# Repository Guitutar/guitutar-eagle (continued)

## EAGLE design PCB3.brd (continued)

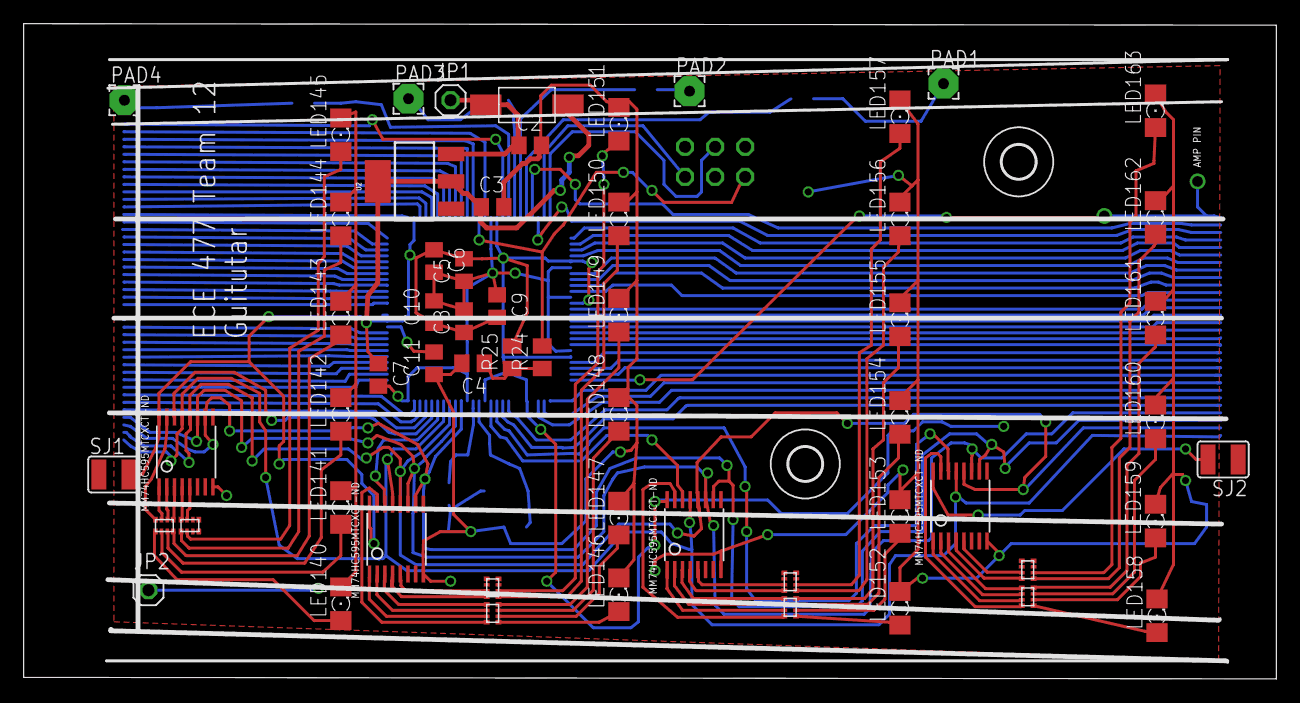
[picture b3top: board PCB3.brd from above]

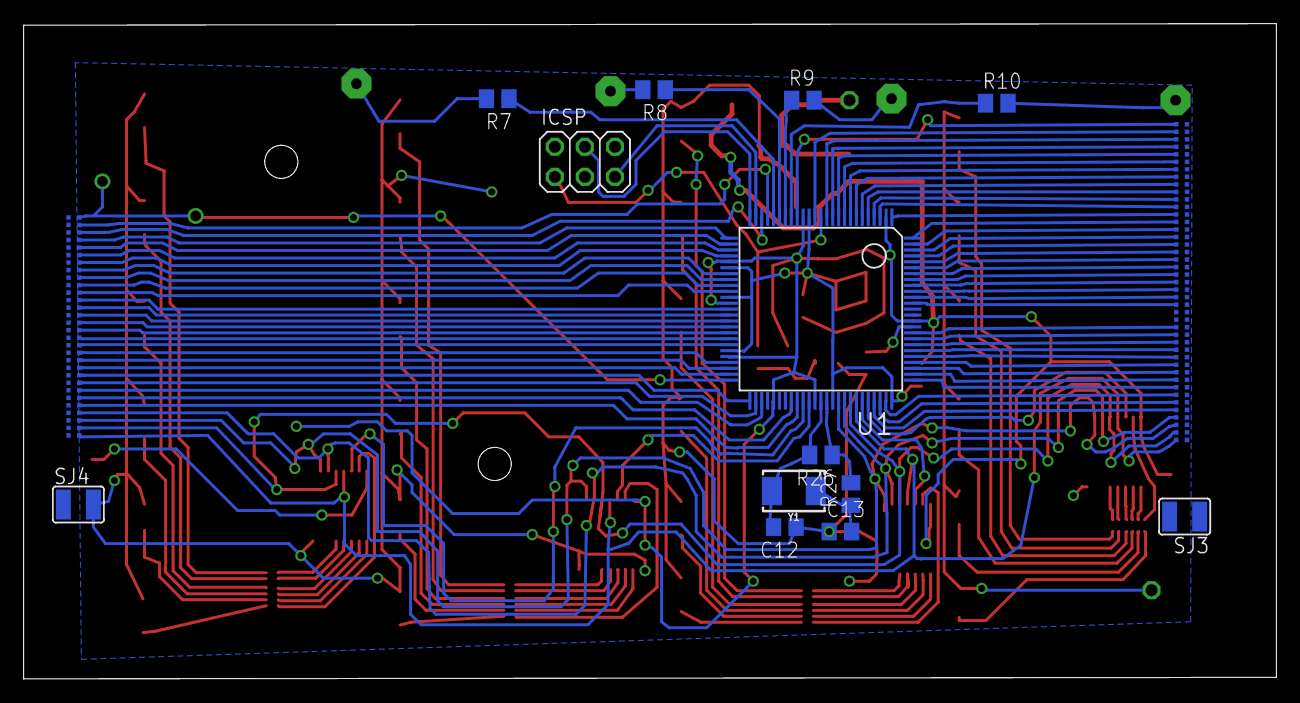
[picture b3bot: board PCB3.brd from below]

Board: 2 copper layers, 105.8 x 55.4 mm, 146 parts (86 on the bottom side), 141 nets.

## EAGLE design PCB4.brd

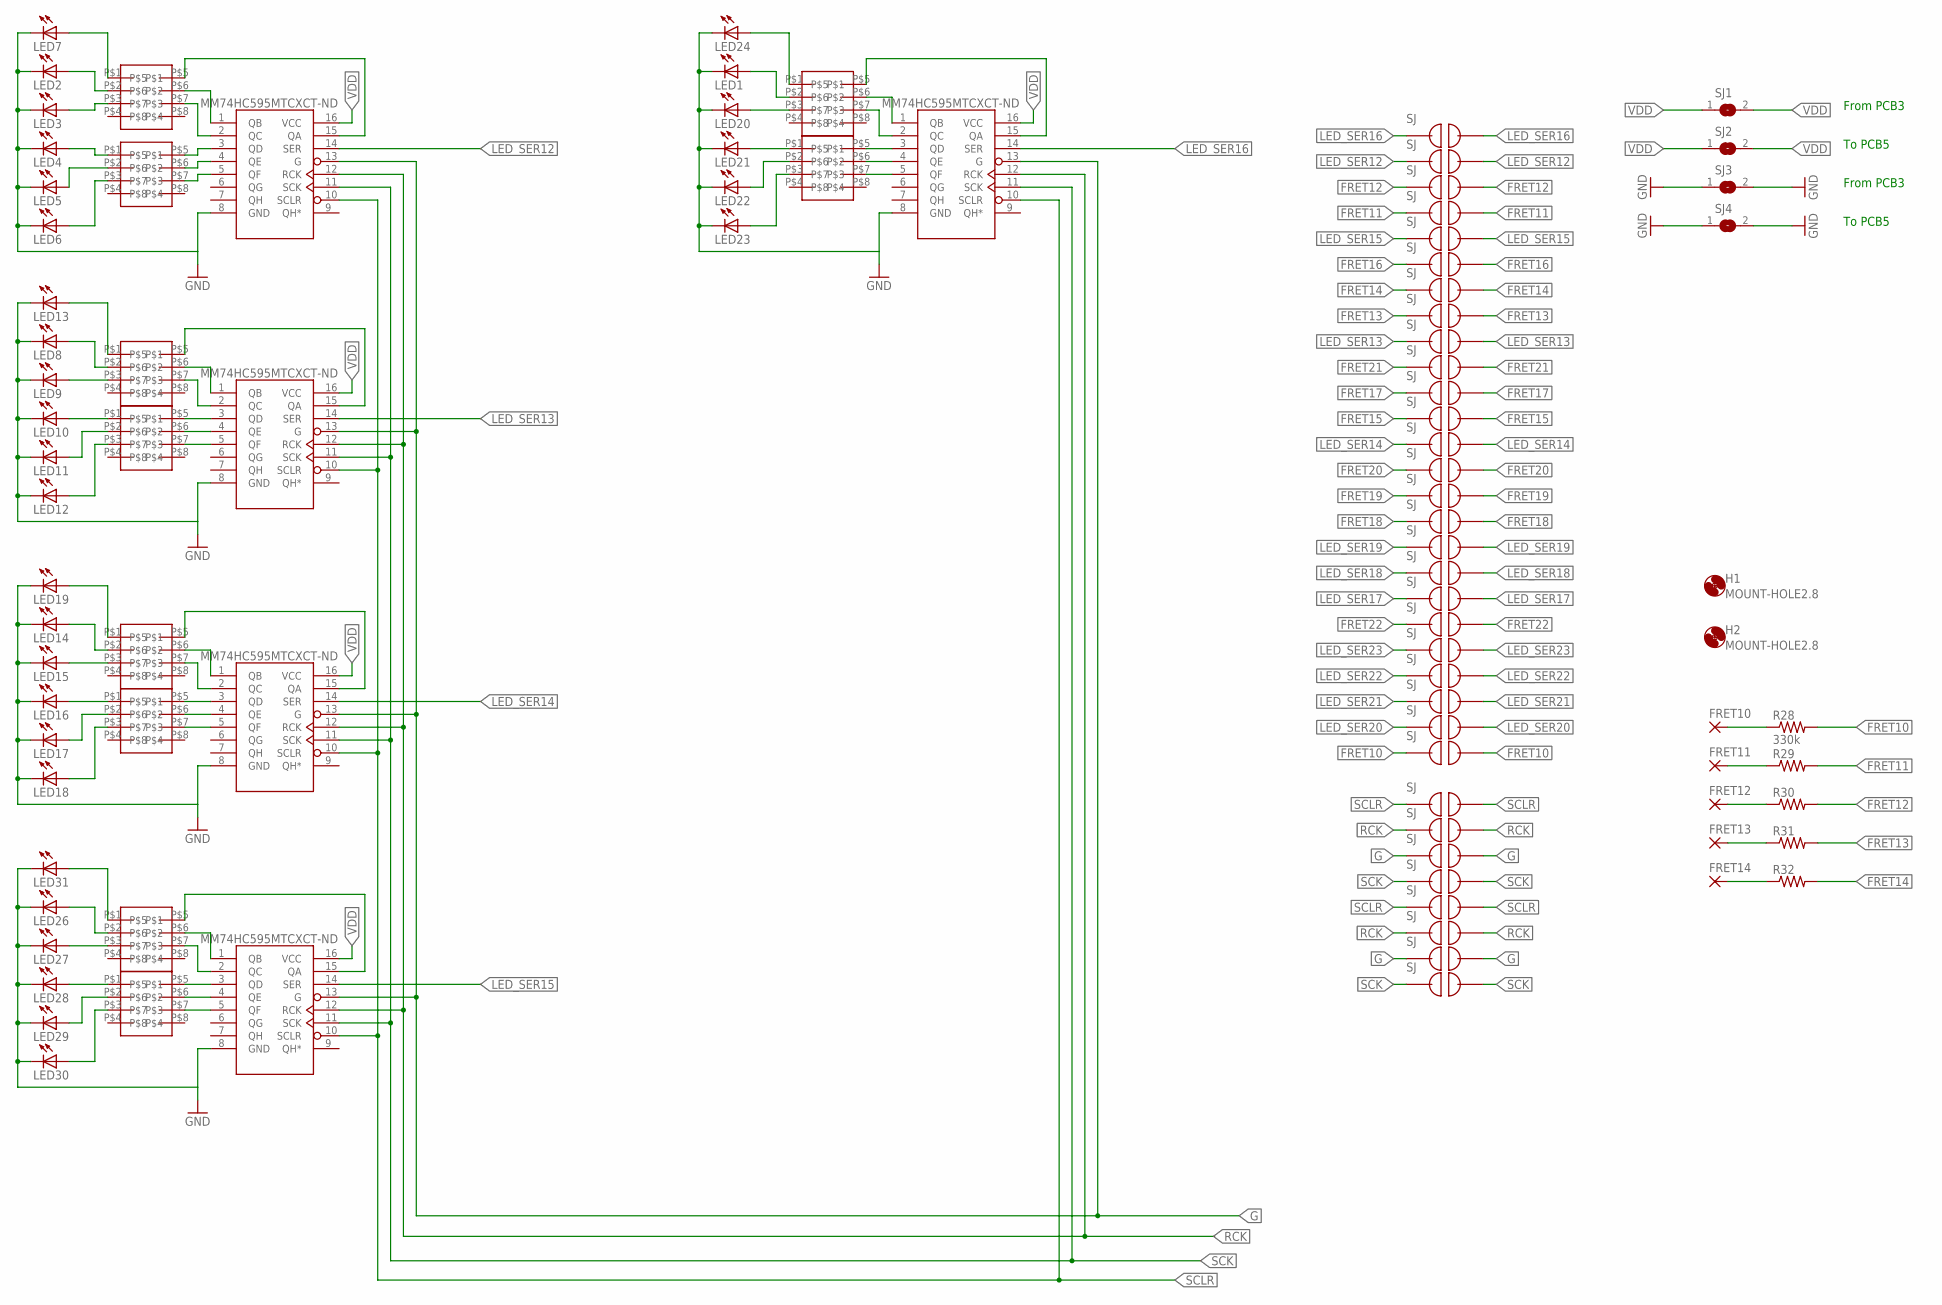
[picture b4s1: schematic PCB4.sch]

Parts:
FRET10, FRET11, FRET12, FRET13, FRET14: 2,54/0,9
H1, H2: MOUNT-HOLE2.8; 2,8
LED1, LED2, LED3, LED4, LED5, LED6, LED7, LED8, LED9, LED10, LED11, LED12, LED13, LED14, LED15, LED16, LED17, LED18, LED19, LED20, LED21, LED22, LED23, LED24, LED26, LED27, LED28, LED29, LED30, LED31: LEDSMT1206; 1206
R28: 330k; R0805
R29, R30, R31, R32: R-US_R0805; R0805
SJ1, SJ2, SJ3, SJ4: SJ
U$1, U$2, U$3, U$4, U$5: MM74HC595TSSOP-LD16; MM74HC595MTCXCT-ND
U$6, U$7, U$8, U$9, U$10, U$11, U$12, U$13, U$14, U$15: MNR04MRAPJ680; MNR04
U$19, U$42, U$45, U$46, U$47, U$48, U$49, U$50, U$51, U$52, U$53, U$54, U$55, U$56, U$57, U$58, U$59, U$60, U$61, U$62, U$63, U$64, U$65, U$66, U$67, U$68, U$69, U$79, U$80, U$81, U$82, U$83, U$84: JUMPER

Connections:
FRET10: R28.2, U$69.P$1, U$69.P$2
FRET11: R29.2, U$48.P$1, U$48.P$2
FRET12: R30.2, U$47.P$1, U$47.P$2
FRET13: R31.2, U$52.P$1, U$52.P$2
FRET14: R32.2, U$51.P$1, U$51.P$2
FRET15: U$56.P$1, U$56.P$2
FRET16: U$50.P$1, U$50.P$2
FRET17: U$55.P$1, U$55.P$2
FRET18: U$60.P$1, U$60.P$2
FRET19: U$59.P$1, U$59.P$2
FRET20: U$58.P$1, U$58.P$2
FRET21: U$54.P$1, U$54.P$2
FRET22: U$64.P$1, U$64.P$2
G: U$1.13 (G), U$2.13 (G), U$3.13 (G), U$4.13 (G), U$5.13 (G), U$80.P$1, U$80.P$2, U$84.P$1, U$84.P$2
GND: LED1.C, LED2.C, LED3.C, LED4.C, LED5.C, LED6.C, LED7.C, LED8.C, LED9.C, LED10.C, LED11.C, LED12.C, LED13.C, LED14.C, LED15.C, LED16.C, LED17.C, LED18.C, LED19.C, LED20.C, LED21.C, LED22.C, LED23.C, LED24.C, LED26.C, LED27.C, LED28.C, LED29.C, LED30.C, LED31.C, SJ3.1, SJ3.2, SJ4.1, SJ4.2, U$1.8 (GND), U$2.8 (GND), U$3.8 (GND), U$4.8 (GND), U$5.8 (GND)
LED_SER12: U$4.14 (SER), U$46.P$1, U$46.P$2
LED_SER13: U$1.14 (SER), U$53.P$1, U$53.P$2
LED_SER14: U$3.14 (SER), U$57.P$1, U$57.P$2
LED_SER15: U$5.14 (SER), U$49.P$1, U$49.P$2
LED_SER16: U$2.14 (SER), U$45.P$1, U$45.P$2
LED_SER17: U$63.P$1, U$63.P$2
LED_SER18: U$62.P$1, U$62.P$2
LED_SER19: U$61.P$1, U$61.P$2
LED_SER20: U$68.P$1, U$68.P$2
LED_SER21: U$67.P$1, U$67.P$2
LED_SER22: U$66.P$1, U$66.P$2
LED_SER23: U$65.P$1, U$65.P$2
unnamed: LED2.A, U$6.P$2
unnamed: U$4.1 (QB), U$6.P$6
unnamed: LED3.A, U$6.P$3
unnamed: U$4.2 (QC), U$6.P$7
unnamed: LED4.A, U$7.P$1
unnamed: LED7.A, U$6.P$1
unnamed: U$4.15 (QA), U$6.P$5
unnamed: LED5.A, U$7.P$2
unnamed: U$4.3 (QD), U$7.P$5
unnamed: U$4.4 (QE), U$7.P$6
unnamed: U$4.5 (QF), U$7.P$7
unnamed: LED6.A, U$7.P$3
unnamed: LED13.A, U$8.P$1
unnamed: LED8.A, U$8.P$2
unnamed: U$1.1 (QB), U$8.P$6
unnamed: U$1.2 (QC), U$8.P$7
unnamed: LED9.A, U$8.P$3
unnamed: LED10.A, U$9.P$1
unnamed: U$1.3 (QD), U$9.P$5
unnamed: LED11.A, U$9.P$2
unnamed: U$1.4 (QE), U$9.P$6
unnamed: U$1.5 (QF), U$9.P$7
unnamed: LED12.A, U$9.P$3
unnamed: U$1.15 (QA), U$8.P$5
unnamed: LED19.A, U$10.P$1
unnamed: LED14.A, U$10.P$2
unnamed: U$3.1 (QB), U$10.P$6
unnamed: U$3.2 (QC), U$10.P$7
unnamed: LED15.A, U$10.P$3
unnamed: LED16.A, U$11.P$1
unnamed: U$3.3 (QD), U$11.P$5
unnamed: U$3.4 (QE), U$11.P$6
unnamed: U$3.5 (QF), U$11.P$7
unnamed: LED18.A, U$11.P$3
unnamed: LED17.A, U$11.P$2
unnamed: LED31.A, U$12.P$1
unnamed: LED26.A, U$12.P$2
unnamed: LED27.A, U$12.P$3
unnamed: U$5.2 (QC), U$12.P$7
unnamed: U$3.15 (QA), U$10.P$5
unnamed: U$5.1 (QB), U$12.P$6
unnamed: U$5.3 (QD), U$13.P$5
unnamed: U$5.4 (QE), U$13.P$6
unnamed: U$5.5 (QF), U$13.P$7
unnamed: U$2.15 (QA), U$14.P$5
unnamed: LED28.A, U$13.P$1
unnamed: LED29.A, U$13.P$2
unnamed: LED30.A, U$13.P$3
unnamed: LED24.A, U$14.P$1
unnamed: LED1.A, U$14.P$2
unnamed: LED20.A, U$14.P$3
unnamed: U$2.1 (QB), U$14.P$6
unnamed: U$2.2 (QC), U$14.P$7
unnamed: U$2.3 (QD), U$15.P$5
unnamed: U$2.4 (QE), U$15.P$6
unnamed: U$2.5 (QF), U$15.P$7
unnamed: LED23.A, U$15.P$3
unnamed: FRET10.1, R28.1
unnamed: FRET11.1, R29.1
unnamed: LED22.A, U$15.P$2
unnamed: LED21.A, U$15.P$1
unnamed: FRET12.1, R30.1
unnamed: FRET13.1, R31.1
unnamed: FRET14.1, R32.1
unnamed: U$5.15 (QA), U$12.P$5
RCK: U$1.12 (RCK), U$2.12 (RCK), U$3.12 (RCK), U$4.12 (RCK), U$5.12 (RCK), U$79.P$1, U$79.P$2, U$83.P$1, U$83.P$2
SCK: U$1.11 (SCK), U$2.11 (SCK), U$3.11 (SCK), U$4.11 (SCK), U$5.11 (SCK), U$42.P$1, U$42.P$2, U$81.P$1, U$81.P$2
SCLR: U$1.10 (SCLR), U$2.10 (SCLR), U$3.10 (SCLR), U$4.10 (SCLR), U$5.10 (SCLR), U$19.P$1, U$19.P$2, U$82.P$1, U$82.P$2
VDD: SJ1.1, SJ1.2, SJ2.1, SJ2.2, U$1.16 (VCC), U$2.16 (VCC), U$3.16 (VCC), U$4.16 (VCC), U$5.16 (VCC)

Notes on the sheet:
From PCB3
To PCB5

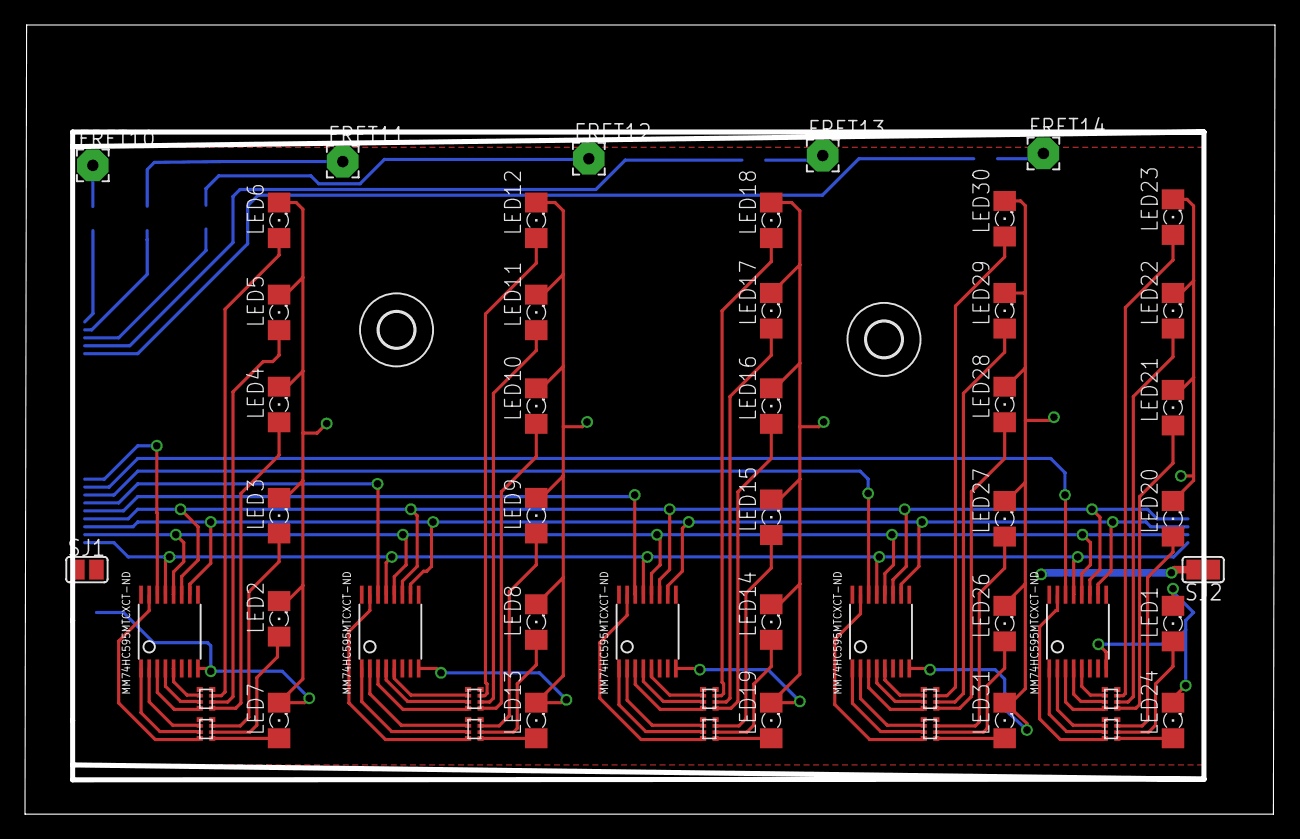
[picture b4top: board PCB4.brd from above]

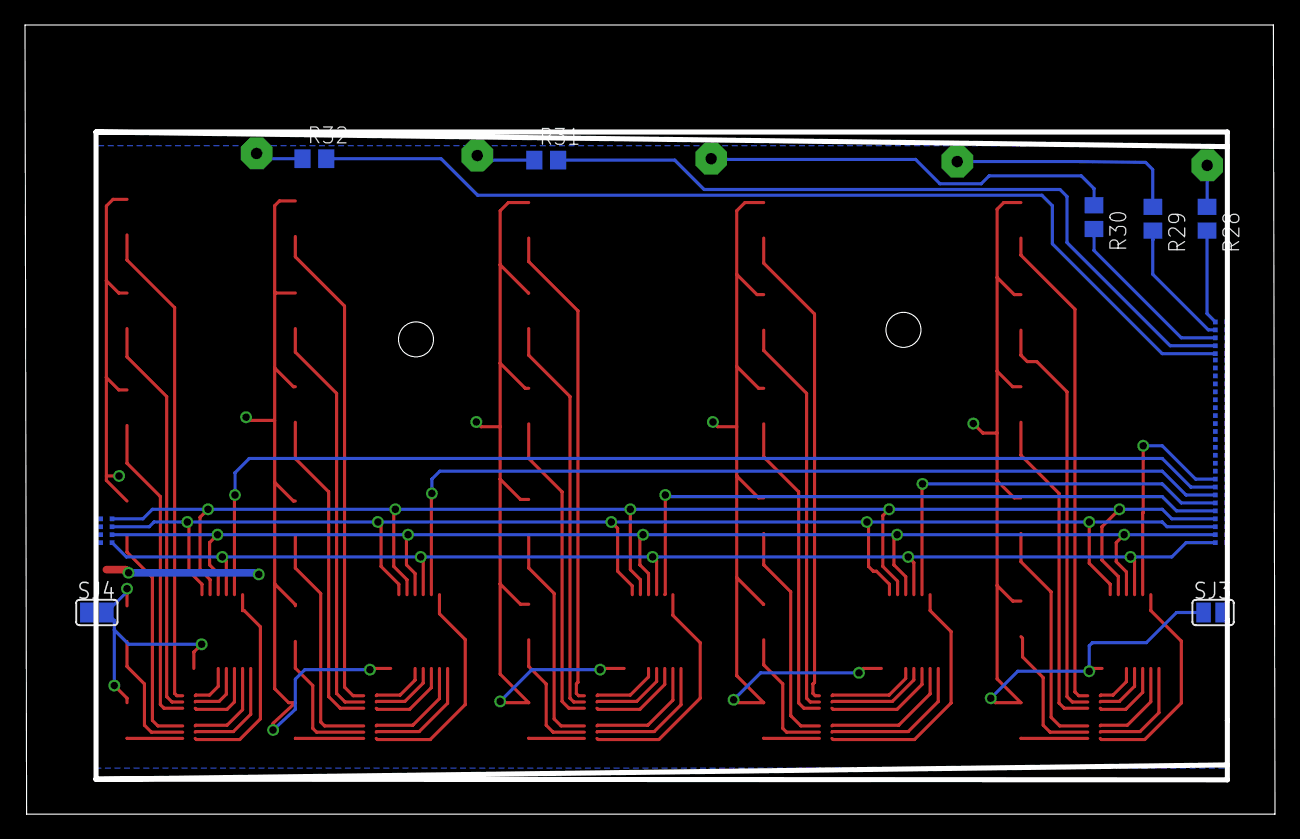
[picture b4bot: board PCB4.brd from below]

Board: 2 copper layers, 100.0 x 63.1 mm, 94 parts (40 on the bottom side), 96 nets.

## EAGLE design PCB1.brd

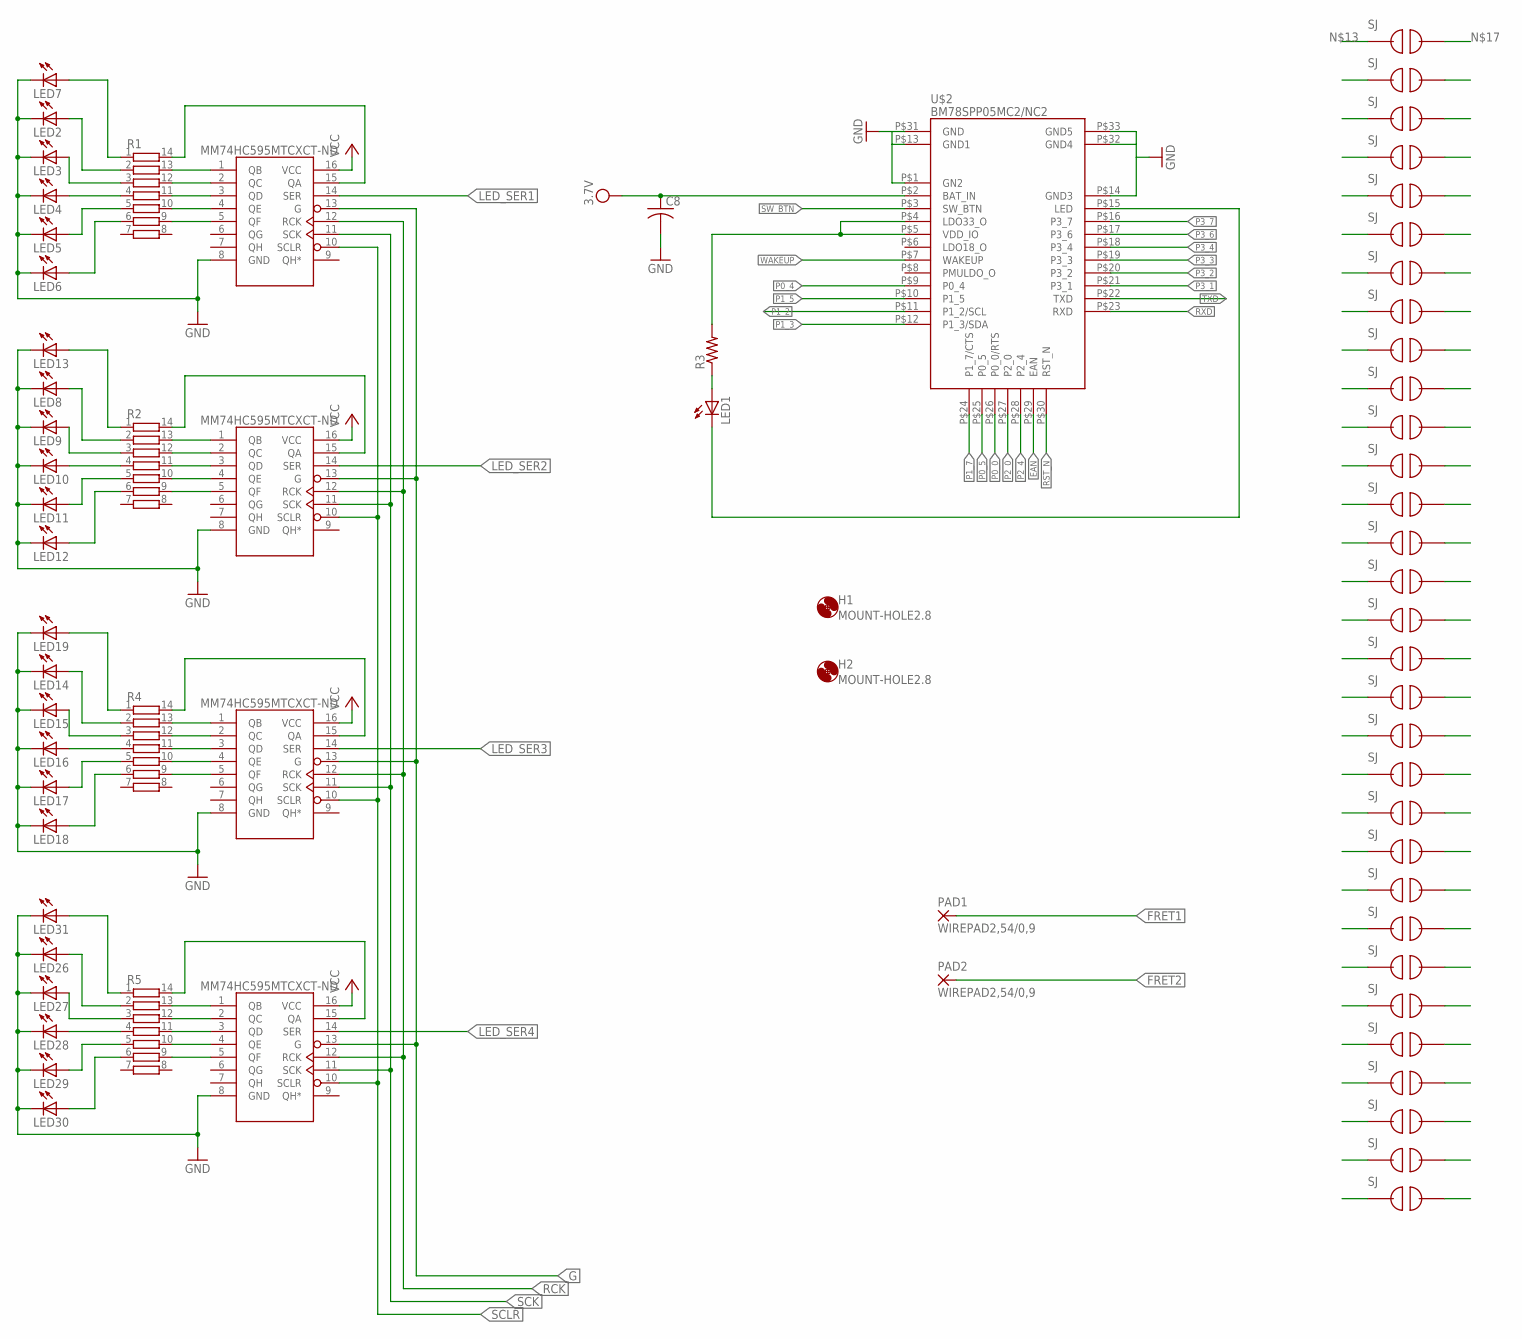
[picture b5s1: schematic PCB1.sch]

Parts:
C8: C-USC0805; C0805
H1, H2: MOUNT-HOLE2.8; 2,8
LED1, LED2, LED3, LED4, LED5, LED6, LED7, LED8, LED9, LED10, LED11, LED12, LED13, LED14, LED15, LED16, LED17, LED18, LED19, LED26, LED27, LED28, LED29, LED30, LED31: LEDSMT1206; 1206
PAD1, PAD2: WIREPAD2,54/0,9; 2,54/0,9
R1, R2, R4, R5: 4814P-T01; 4814P
R3: R-US_M0805; M0805
U$1, U$3, U$4, U$5: MM74HC595TSSOP-LD16; MM74HC595MTCXCT-ND
U$2: BM78SPP05MC2/NC2
U$6, U$7, U$8, U$9, U$10, U$11, U$12, U$13, U$14, U$15, U$16, U$17, U$18, U$19, U$20, U$21, U$22, U$23, U$24, U$25, U$26, U$27, U$28, U$29, U$30, U$31, U$32, U$33, U$34, U$35, U$36: JUMPER

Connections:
EAN: U$2.P$29 (EAN)
FRET1: PAD1.1
FRET2: PAD2.1
G: U$1.13 (G), U$3.13 (G), U$4.13 (G), U$5.13 (G)
GND: C8.2, LED2.C, LED3.C, LED4.C, LED5.C, LED6.C, LED7.C, LED8.C, LED9.C, LED10.C, LED11.C, LED12.C, LED13.C, LED14.C, LED15.C, LED16.C, LED17.C, LED18.C, LED19.C, LED26.C, LED27.C, LED28.C, LED29.C, LED30.C, LED31.C, U$1.8 (GND), U$2.P$1 (GN2), U$2.P$13 (GND1), U$2.P$14 (GND3), U$2.P$31 (GND), U$2.P$32 (GND4), U$2.P$33 (GND5), U$3.8 (GND), U$4.8 (GND), U$5.8 (GND)
LED: LED1.C, U$2.P$15 (LED)
LED_SER1: U$4.14 (SER)
LED_SER2: U$1.14 (SER)
LED_SER3: U$3.14 (SER)
LED_SER4: U$5.14 (SER)
unnamed: R1.13, U$4.1 (QB)
unnamed: R1.12, U$4.2 (QC)
unnamed: R1.11, U$4.3 (QD)
unnamed: R1.10, U$4.4 (QE)
unnamed: R1.9, U$4.5 (QF)
unnamed: LED7.A, R1.1
unnamed: R1.14, U$4.15 (QA)
unnamed: LED2.A, R1.2
unnamed: LED3.A, R1.3
unnamed: LED4.A, R1.4
unnamed: LED5.A, R1.5
unnamed: LED6.A, R1.6
unnamed: LED1.A, R3.1
unnamed: R3.2, U$2.P$4 (LDO33_O), U$2.P$5 (VDD_IO)
unnamed: R2.13, U$1.1 (QB)
unnamed: R2.12, U$1.2 (QC)
unnamed: R2.11, U$1.3 (QD)
unnamed: R2.10, U$1.4 (QE)
unnamed: R2.9, U$1.5 (QF)
unnamed: R2.14, U$1.15 (QA)
unnamed: LED13.A, R2.1
unnamed: LED8.A, R2.2
unnamed: LED9.A, R2.3
unnamed: LED10.A, R2.4
unnamed: LED11.A, R2.5
unnamed: LED12.A, R2.6
unnamed: R4.13, U$3.1 (QB)
unnamed: R4.12, U$3.2 (QC)
unnamed: R4.11, U$3.3 (QD)
unnamed: R4.10, U$3.4 (QE)
unnamed: R4.9, U$3.5 (QF)
unnamed: R4.14, U$3.15 (QA)
unnamed: LED19.A, R4.1
unnamed: LED14.A, R4.2
unnamed: LED15.A, R4.3
unnamed: LED16.A, R4.4
unnamed: LED17.A, R4.5
unnamed: LED18.A, R4.6
unnamed: R5.13, U$5.1 (QB)
unnamed: R5.12, U$5.2 (QC)
unnamed: R5.11, U$5.3 (QD)
unnamed: R5.10, U$5.4 (QE)
unnamed: R5.9, U$5.5 (QF)
unnamed: R5.14, U$5.15 (QA)
unnamed: LED31.A, R5.1
unnamed: LED26.A, R5.2
unnamed: LED27.A, R5.3
unnamed: LED28.A, R5.4
unnamed: LED29.A, R5.5
unnamed: LED30.A, R5.6
P0_0: U$2.P$26 (P0_0/RTS)
P0_4: U$2.P$9 (P0_4)
P0_5: U$2.P$25 (P0_5)
P1_2: U$2.P$11 (P1_2/SCL)
P1_3: U$2.P$12 (P1_3/SDA)
P1_5: U$2.P$10 (P1_5)
P1_7: U$2.P$24 (P1_7/CTS)
P2_0: U$2.P$27 (P2_0)
P2_4: U$2.P$28 (P2_4)
P3_1: U$2.P$21 (P3_1)
P3_2: U$2.P$20 (P3_2)
P3_3: U$2.P$19 (P3_3)
P3_4: U$2.P$18 (P3_4)
P3_6: U$2.P$17 (P3_6)
P3_7: U$2.P$16 (P3_7)
RCK: U$1.12 (RCK), U$3.12 (RCK), U$4.12 (RCK), U$5.12 (RCK)
RST_N: U$2.P$30 (RST_N)
RXD: U$2.P$23 (RXD)
SCK: U$1.11 (SCK), U$3.11 (SCK), U$4.11 (SCK), U$5.11 (SCK)
SCLR: U$1.10 (SCLR), U$3.10 (SCLR), U$4.10 (SCLR), U$5.10 (SCLR)
SW_BTN: U$2.P$3 (SW_BTN)
TXD: U$2.P$22 (TXD)
VCC: U$1.16 (VCC), U$3.16 (VCC), U$4.16 (VCC), U$5.16 (VCC)
VDD: C8.1, U$2.P$2 (BAT_IN)
WAKEUP: U$2.P$7 (WAKEUP)

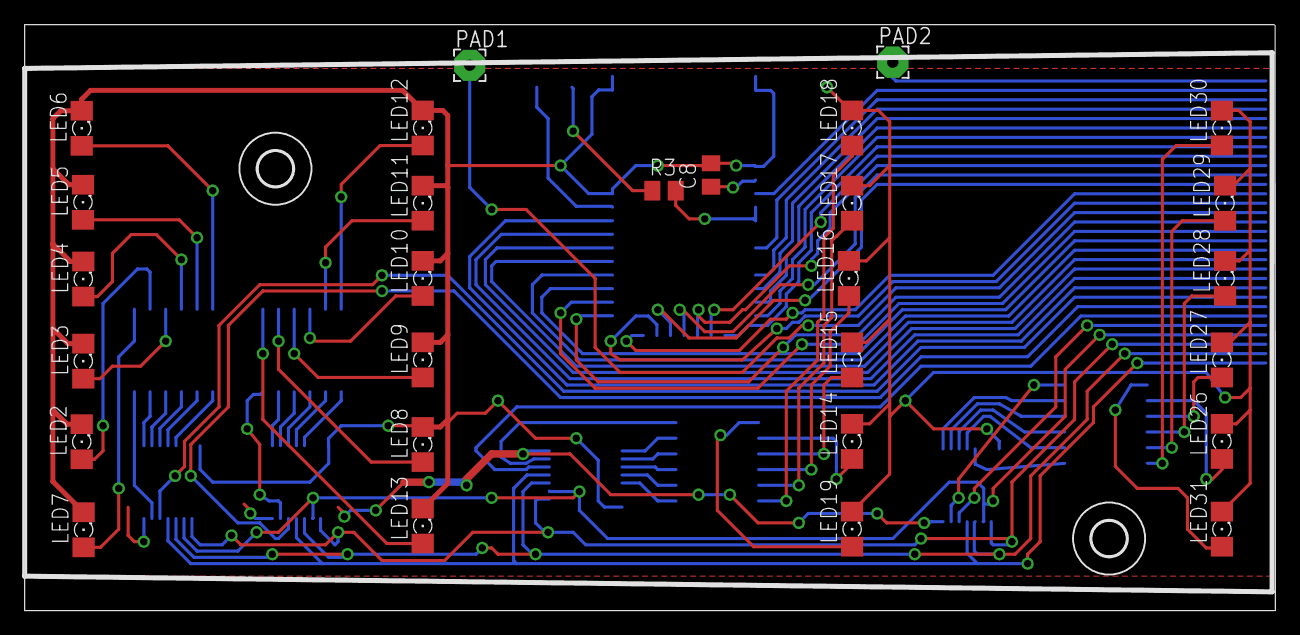
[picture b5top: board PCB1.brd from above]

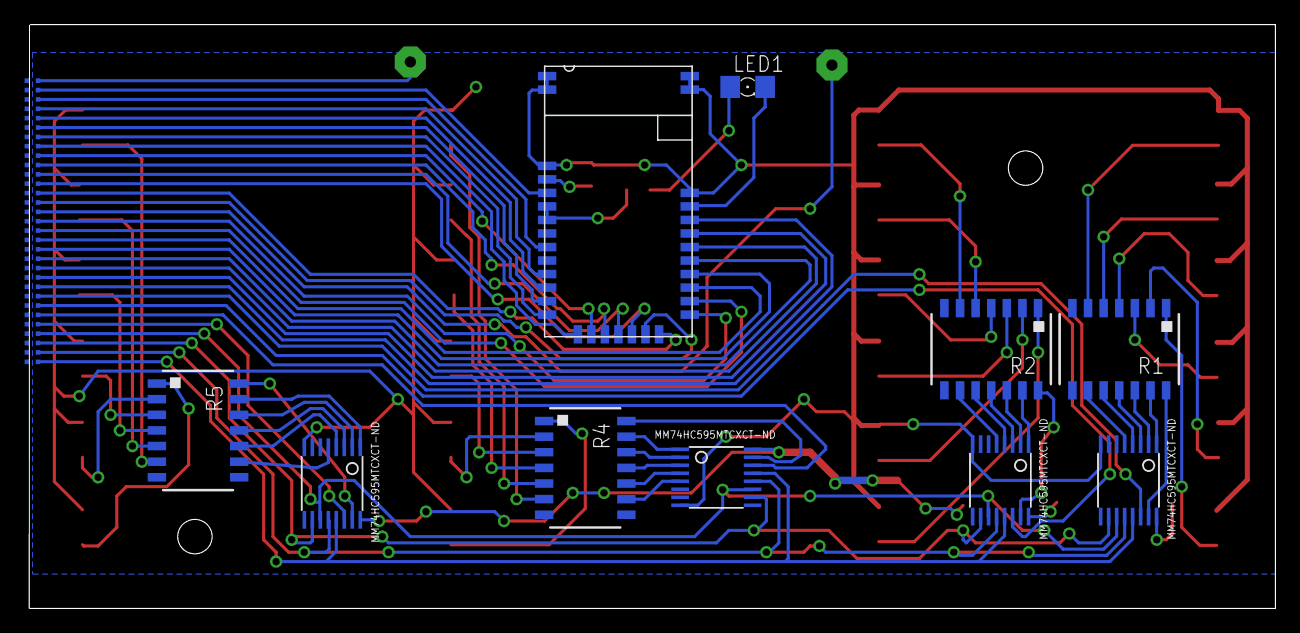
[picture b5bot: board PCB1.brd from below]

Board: 2 copper layers, 101.4 x 47.5 mm, 71 parts (41 on the bottom side), 58 nets.

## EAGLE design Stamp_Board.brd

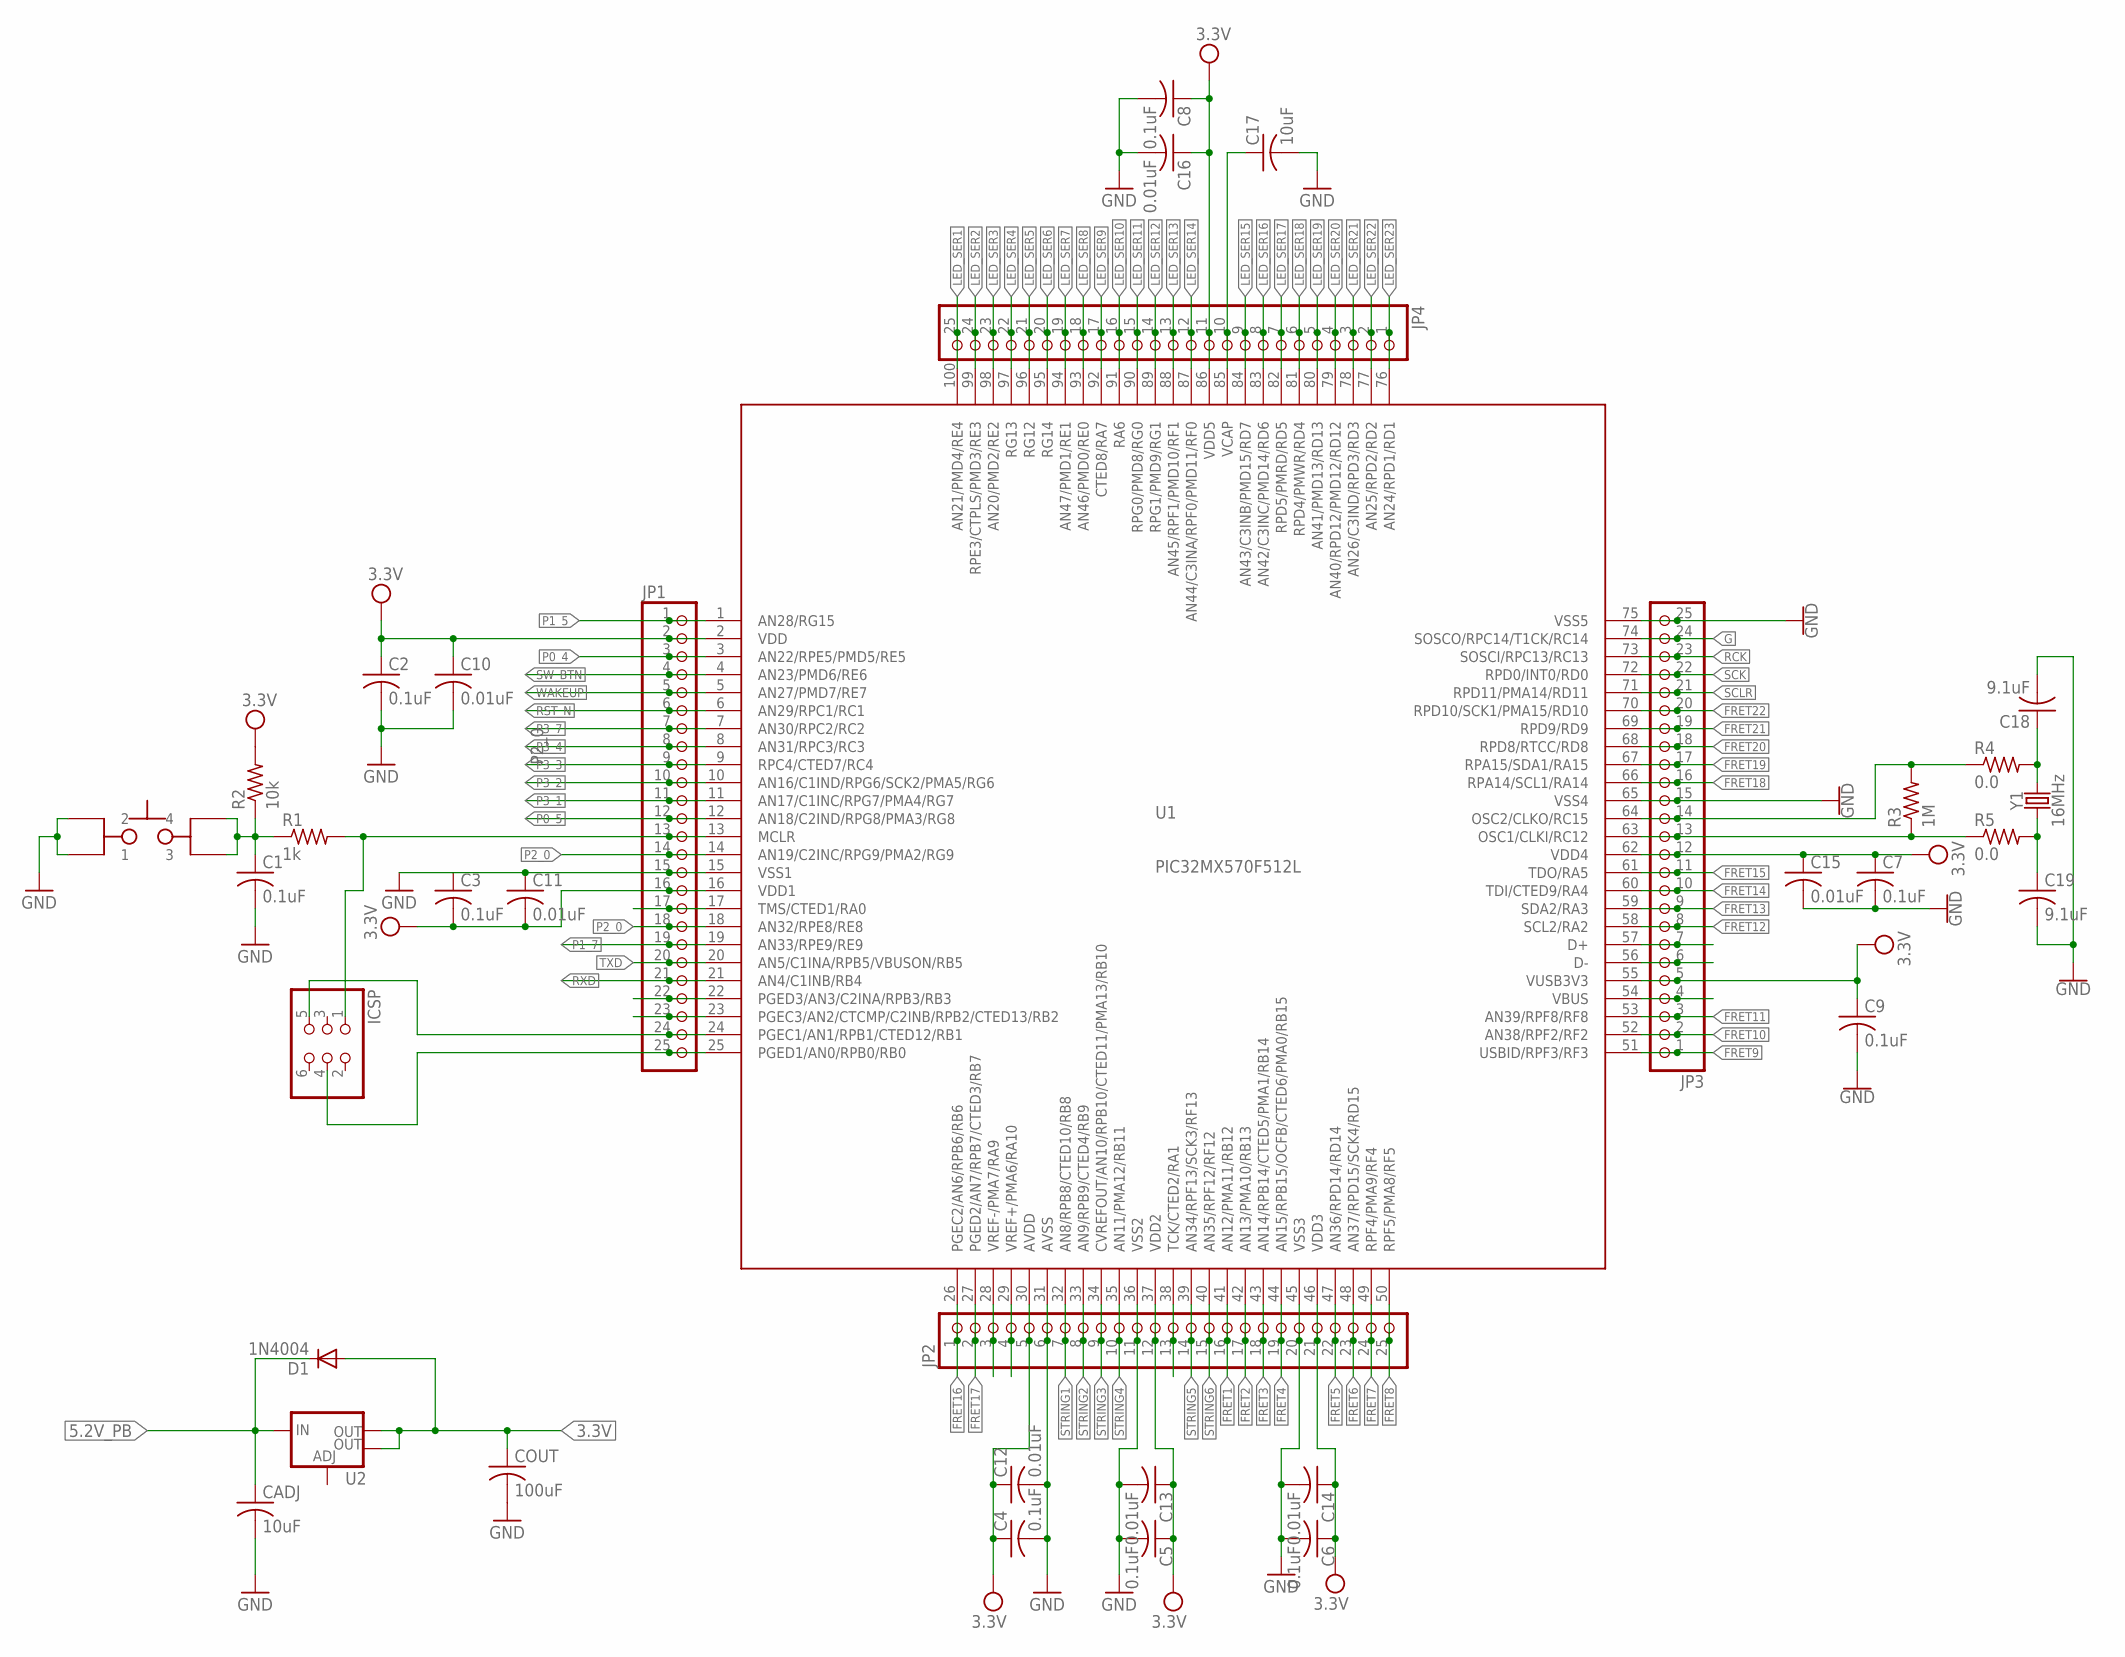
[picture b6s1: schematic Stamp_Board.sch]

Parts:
C1, C2, C3, C4, C5, C6, C7, C8, C9: 0.1uF; C0805
C10, C11, C12, C13, C14, C15, C16: 0.01uF; C0805
C17: 10uF; C0805
C18, C19: 9.1uF; C0805
CADJ: 10uF; C0805
COUT: 100uF; C0805
D1: 1N4004; DO41-10
ICSP: PINHD-2X3; 2X03
JP1, JP2, JP3, JP4: PINHD-1X25; 1X25
R1: 1k; M0805
R2: 10k; M0805
R3: 1M; M0805
R4, R5: 0.0; R0805
S1: LL3301NF065QG
U1: PIC32MX570F512L; TQFP100-14X14
U2: V_REG_LM1117SOT223; SOT223
Y1: 16MHz; CRYSTAL-SMD-5X3.2-2PAD

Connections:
3.3V: COUT.1, D1.A, U2.2 (OUT), U2.4 (OUT)
5.2V_PB: CADJ.1, D1.C, U2.3 (IN)
FRET1: JP2.16, U1.41 (AN12/PMA11/RB12)
FRET2: JP2.17, U1.42 (AN13/PMA10/RB13)
FRET3: JP2.18, U1.43 (AN14/RPB14/CTED5/PMA1/RB14)
FRET4: JP2.19, U1.44 (AN15/RPB15/OCFB/CTED6/PMA0/RB15)
FRET5: JP2.22, U1.47 (AN36/RPD14/RD14)
FRET6: JP2.23, U1.48 (AN37/RPD15/SCK4/RD15)
FRET7: JP2.24, U1.49 (RPF4/PMA9/RF4)
FRET8: JP2.25, U1.50 (RPF5/PMA8/RF5)
FRET9: JP3.1, U1.51 (USBID/RPF3/RF3)
FRET10: JP3.2, U1.52 (AN38/RPF2/RF2)
FRET11: JP3.3, U1.53 (AN39/RPF8/RF8)
FRET12: JP3.8, U1.58 (SCL2/RA2)
FRET13: JP3.9, U1.59 (SDA2/RA3)
FRET14: JP3.10, U1.60 (TDI/CTED9/RA4)
FRET15: JP3.11, U1.61 (TDO/RA5)
FRET16: JP2.1, U1.26 (PGEC2/AN6/RPB6/RB6)
FRET17: JP2.2, U1.27 (PGED2/AN7/RPB7/CTED3/RB7)
FRET18: JP3.16, U1.66 (RPA14/SCL1/RA14)
FRET19: JP3.17, U1.67 (RPA15/SDA1/RA15)
FRET20: JP3.18, U1.68 (RPD8/RTCC/RD8)
FRET21: JP3.19, U1.69 (RPD9/RD9)
FRET22: JP3.20, U1.70 (RPD10/SCK1/PMA15/RD10)
G: JP3.24, U1.74 (SOSCO/RPC14/T1CK/RC14)
GND: C1.2, C2.2, C3.1, C4.2, C5.2, C6.2, C7.2, C8.2, C9.2, C10.2, C11.1, C12.2, C13.2, C14.2, C15.2, C16.2, C17.2, C18.2, C19.2, CADJ.2, COUT.2, JP1.15, JP2.6, JP2.11, JP2.20, JP3.15, JP3.25, S1.P$1 (1), S1.P$2 (2), U1.15 (VSS1), U1.31 (AVSS), U1.36 (VSS2), U1.45 (VSS3), U1.65 (VSS4), U1.75 (VSS5)
LED_SER1: JP4.25, U1.100 (AN21/PMD4/RE4)
LED_SER2: JP4.24, U1.99 (RPE3/CTPLS/PMD3/RE3)
LED_SER3: JP4.23, U1.98 (AN20/PMD2/RE2)
LED_SER4: JP4.22, U1.97 (RG13)
LED_SER5: JP4.21, U1.96 (RG12)
LED_SER6: JP4.20, U1.95 (RG14)
LED_SER7: JP4.19, U1.94 (AN47/PMD1/RE1)
LED_SER8: JP4.18, U1.93 (AN46/PMD0/RE0)
LED_SER9: JP4.17, U1.92 (CTED8/RA7)
LED_SER10: JP4.16, U1.91 (RA6)
LED_SER11: JP4.15, U1.90 (RPG0/PMD8/RG0)
LED_SER12: JP4.14, U1.89 (RPG1/PMD9/RG1)
LED_SER13: JP4.13, U1.88 (AN45/RPF1/PMD10/RF1)
LED_SER14: JP4.12, U1.87 (AN44/C3INA/RPF0/PMD11/RF0)
LED_SER15: JP4.9, U1.84 (AN43/C3INB/PMD15/RD7)
LED_SER16: JP4.8, U1.83 (AN42/C3INC/PMD14/RD6)
LED_SER17: JP4.7, U1.82 (RPD5/PMRD/RD5)
LED_SER18: JP4.6, U1.81 (RPD4/PMWR/RD4)
LED_SER19: JP4.5, U1.80 (AN41/PMD13/RD13)
LED_SER20: JP4.4, U1.79 (AN40/RPD12/PMD12/RD12)
LED_SER21: JP4.3, U1.78 (AN26/C3IND/RPD3/RD3)
LED_SER22: JP4.2, U1.77 (AN25/RPD2/RD2)
LED_SER23: JP4.1, U1.76 (AN24/RPD1/RD1)
unnamed: JP3.14, R3.2, R4.1, U1.64 (OSC2/CLKO/RC15)
unnamed: ICSP.5, JP1.24, U1.24 (PGEC1/AN1/RPB1/CTED12/RB1)
unnamed: JP1.17, U1.17 (TMS/CTED1/RA0)
unnamed: JP1.22, U1.22 (PGED3/AN3/C2INA/RPB3/RB3)
unnamed: JP1.23, U1.23 (PGEC3/AN2/CTCMP/C2INB/RPB2/CTED13/RB2)
unnamed: C18.1, R4.2, Y1.P$2 (2)
unnamed: C19.1, R5.2, Y1.P$1 (1)
unnamed: C17.1, JP4.10, U1.85 (VCAP)
unnamed: ICSP.1, JP1.13, R1.2, U1.13 (MCLR)
unnamed: ICSP.4, JP1.25, U1.25 (PGED1/AN0/RPB0/RB0)
unnamed: JP3.13, R3.1, R5.1, U1.63 (OSC1/CLKI/RC12)
unnamed: C1.1, R1.1, R2.1, S1.P$3 (3), S1.P$4 (4)
unnamed: JP2.3, U1.28 (VREF-/PMA7/RA9)
unnamed: JP2.4, U1.29 (VREF+/PMA6/RA10)
unnamed: JP2.13, U1.38 (TCK/CTED2/RA1)
unnamed: JP3.4, U1.54 (VBUS)
unnamed: JP3.6, U1.56 (D-)
unnamed: JP3.7, U1.57 (D+)
P0_4: JP1.3, U1.3 (AN22/RPE5/PMD5/RE5)
P0_5: JP1.12, U1.12 (AN18/C2IND/RPG8/PMA3/RG8)
P1_5: JP1.1, U1.1 (AN28/RG15)
P1_7: JP1.19, U1.19 (AN33/RPE9/RE9)
P2_0: JP1.14, JP1.18, U1.14 (AN19/C2INC/RPG9/PMA2/RG9), U1.18 (AN32/RPE8/RE8)
P3_1: JP1.11, U1.11 (AN17/C1INC/RPG7/PMA4/RG7)
P3_2: JP1.10, U1.10 (AN16/C1IND/RPG6/SCK2/PMA5/RG6)
P3_3: JP1.9, U1.9 (RPC4/CTED7/RC4)
P3_4: JP1.8, U1.8 (AN31/RPC3/RC3)
P3_7: JP1.7, U1.7 (AN30/RPC2/RC2)
RCK: JP3.23, U1.73 (SOSCI/RPC13/RC13)
RST_N: JP1.6, U1.6 (AN29/RPC1/RC1)
RXD: JP1.21, U1.21 (AN4/C1INB/RB4)
SCK: JP3.22, U1.72 (RPD0/INT0/RD0)
SCLR: JP3.21, U1.71 (RPD11/PMA14/RD11)
STRING1: JP2.7, U1.32 (AN8/RPB8/CTED10/RB8)
STRING2: JP2.8, U1.33 (AN9/RPB9/CTED4/RB9)
STRING3: JP2.9, U1.34 (CVREFOUT/AN10/RPB10/CTED11/PMA13/RB10)
STRING4: JP2.10, U1.35 (AN11/PMA12/RB11)
STRING5: JP2.14, U1.39 (AN34/RPF13/SCK3/RF13)
STRING6: JP2.15, U1.40 (AN35/RPF12/RF12)
SW_BTN: JP1.4, U1.4 (AN23/PMD6/RE6)
TXD: JP1.20, U1.20 (AN5/C1INA/RPB5/VBUSON/RB5)
VDD: C2.1, C3.2, C4.1, C5.1, C6.1, C7.1, C8.1, C9.1, C10.1, C11.2, C12.1, C13.1, C14.1, C15.1, C16.1, JP1.2, JP1.16, JP2.5, JP2.12, JP2.21, JP3.5, JP3.12, JP4.11, R2.2, U1.2 (VDD), U1.16 (VDD1), U1.30 (AVDD), U1.37 (VDD2), U1.46 (VDD3), U1.55 (VUSB3V3), U1.62 (VDD4), U1.86 (VDD5)
WAKEUP: JP1.5, U1.5 (AN27/PMD7/RE7)
